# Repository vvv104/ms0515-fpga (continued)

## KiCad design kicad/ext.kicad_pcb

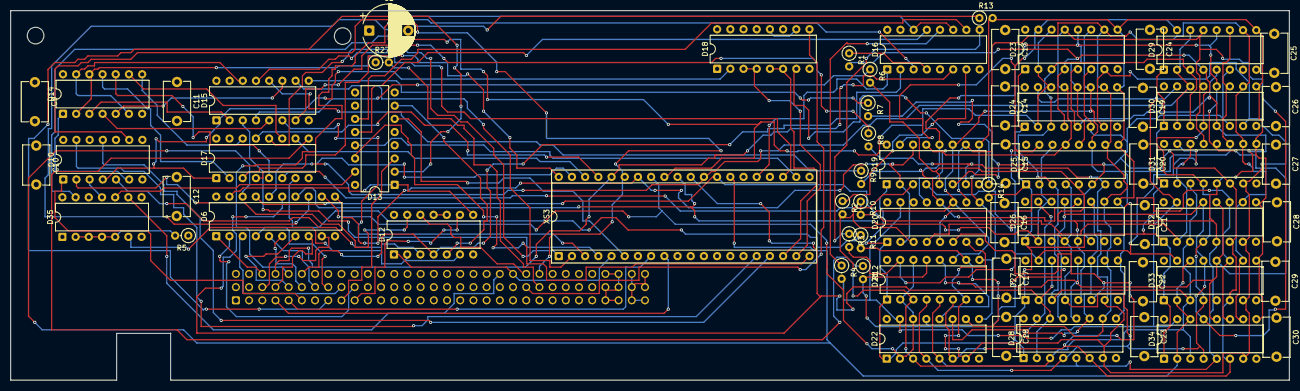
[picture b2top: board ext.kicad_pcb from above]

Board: 4 copper layers, 246.1 x 71.1 mm, 68 parts (1 on the bottom side), 102 nets.

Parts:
C1: 16В 33 мкФ ±20%; CP_Radial_D10.0mm_P7.50mm
C9, C10, C11, C12, C13, C14, C15, C16, C17, C18, C19, C20, C21, C22, C23, C24, C25, C26, C27, C28, C29, C30: 0,1 мкФ; C_Disc_D7.5mm_W5.0mm_P7.50mm
D6: К555АП6; DIP-20_W7.62mm
D10: К555ЛН1; DIP-14_W7.62mm
D12: К555ЛЛ1; DIP-14_W7.62mm
D13: КР531ИД14; DIP-16_W7.62mm
D14: К555ИЕ19; DIP-14_W7.62mm
D15, D16, D17: К555КП11; DIP-16_W7.62mm
D18: К555КП2; DIP-16_W7.62mm
D19, D20, D21, D22, D23, D24, D25, D26, D27, D28, D29, D30, D31, D32, D33, D34: КР565РУ7Г; DIP-16_W7.62mm
D35: К555ИР16; DIP-14_W7.62mm
H1, H2: Hole_3.2mm_NPTH
R1, R2, R3, R4, R6, R7, R8, R9, R10, R11, R12, R13, R14: 33 Ом; R_Axial_DIN0207_L6.3mm_D2.5mm_P2.54mm_Vertical
R5, R27: 4,7 кОм; R_Axial_DIN0207_L6.3mm_D2.5mm_P2.54mm_Vertical
XP1: plug, 96 (rows A, B, C of 32); DIN41612_C_3x32_Male_Horizontal_THT
XS3: DIP socket for D2; DIP-40_W15.24mm_Socket

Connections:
+5V: C1.1, C9.1, C10.1, C11.1, C12.1, C13.1, C14.1, C15.1, C16.1, C17.1, C18.1, C19.1, C20.1, C21.1, C22.1, C23.1, C24.1, C25.1, C26.1, C27.1, C28.1, C29.1, C30.1, D6.20, D10.14, D12.14, D13.16, D14.14, D15.16, D16.5, D16.16, D17.16, D18.16, D19.8, D20.8, D21.8, D22.8, D23.8, D24.8, D25.8, D26.8, D27.8, D28.8, D29.8, D30.8, D31.8, D32.8, D33.8, D34.8, D35.8, D35.14, R5.1, R27.1, XP1.a27, XP1.a28, XP1.b27, XP1.b28, XP1.c27, XP1.c28, XS3.26
+12V: XP1.a29, XP1.a30, XP1.b29, XP1.b30, XP1.c29, XP1.c30
-12V: XP1.a31, XP1.a32, XP1.b31, XP1.b32, XP1.c31, XP1.c32
CAS0: D19.15, D21.15, D23.15, D25.15, D27.15, D29.15, D31.15, D33.15, R3.2
CAS1: D20.15, D22.15, D24.15, D26.15, D28.15, D30.15, D32.15, D34.15, R4.2
CTS_B: D18.9, XP1.b23
DTR: D10.13, XS3.16
GND: C1.2, C9.2, C10.2, C11.2, C12.2, C13.2, C14.2, C15.2, C16.2, C17.2, C18.2, C19.2, C20.2, C21.2, C22.2, C23.2, C24.2, C25.2, C26.2, C27.2, C28.2, C29.2, C30.2, D6.10, D10.7, D12.7, D13.8, D14.7, D15.8, D15.15, D16.8, D16.15, D17.8, D17.15, D18.1, D18.8, D18.11, D18.13, D18.15, D19.16, D20.16, D21.16, D22.16, D23.16, D24.16, D25.16, D26.16, D27.16, D28.16, D29.16, D30.16, D31.16, D32.16, D33.16, D34.16, D35.1, D35.7, XP1.a1, XP1.a2, XP1.a19, XP1.a20, XP1.a25, XP1.a26, XP1.b1, XP1.b2, XP1.b19, XP1.b20, XP1.b25, XP1.b26, XP1.c1, XP1.c2, XP1.c15, XP1.c16, XP1.c25, XP1.c26, XS3.7
MA00: D14.3, D15.2
MA01: D14.4, D15.5
MA02: D14.5, D15.11
MA03: D14.6, D14.13, D15.14
MA04: D14.11, D17.2
MA05: D14.10, D17.5
MA06: D14.9, D17.11
MA07: D14.8, D17.14
MA08: D15.3, XS3.4
MA09: D15.6, XS3.3
MA10: D15.10, XS3.2
MA11: D15.13, XS3.1
MA12: D17.3, XS3.40
MA13: D17.6, XS3.39
MA14: D17.10, XS3.38
MA15: D17.13, XS3.37
MA16: D18.5, D18.6, XS3.18
MA17: D18.3, D18.4, XS3.19
RA0: D19.5, D20.5, D21.5, D22.5, D23.5, D24.5, D25.5, D26.5, D27.5, D28.5, D29.5, D30.5, D31.5, D32.5, D33.5, D34.5, R6.2
RA1: D19.7, D20.7, D21.7, D22.7, D23.7, D24.7, D25.7, D26.7, D27.7, D28.7, D29.7, D30.7, D31.7, D32.7, D33.7, D34.7, R8.2
RA2: D19.6, D20.6, D21.6, D22.6, D23.6, D24.6, D25.6, D26.6, D27.6, D28.6, D29.6, D30.6, D31.6, D32.6, D33.6, D34.6, R7.2
RA3: D19.12, D20.12, D21.12, D22.12, D23.12, D24.12, D25.12, D26.12, D27.12, D28.12, D29.12, D30.12, D31.12, D32.12, D33.12, D34.12, R9.2
RA4: D19.11, D20.11, D21.11, D22.11, D23.11, D24.11, D25.11, D26.11, D27.11, D28.11, D29.11, D30.11, D31.11, D32.11, D33.11, D34.11, R10.2
RA5: D19.10, D20.10, D21.10, D22.10, D23.10, D24.10, D25.10, D26.10, D27.10, D28.10, D29.10, D30.10, D31.10, D32.10, D33.10, D34.10, R11.2
RA6: D19.13, D20.13, D21.13, D22.13, D23.13, D24.13, D25.13, D26.13, D27.13, D28.13, D29.13, D30.13, D31.13, D32.13, D33.13, D34.13, R12.2
RA7: D19.9, D20.9, D21.9, D22.9, D23.9, D24.9, D25.9, D26.9, D27.9, D28.9, D29.9, D30.9, D31.9, D32.9, D33.9, D34.9, R13.2
RA8: D19.1, D20.1, D21.1, D22.1, D23.1, D24.1, D25.1, D26.1, D27.1, D28.1, D29.1, D30.1, D31.1, D32.1, D33.1, D34.1, R14.2
RAS: D19.4, D20.4, D21.4, D22.4, D23.4, D24.4, D25.4, D26.4, D27.4, D28.4, D29.4, D30.4, D31.4, D32.4, D33.4, D34.4, R1.2
RAS ОЗУ: D16.3, D35.13
RTS: D10.11, XS3.17
TC15: D35.9, XP1.c21
WE: D19.3, D20.3, D21.3, D22.3, D23.3, D24.3, D25.3, D26.3, D27.3, D28.3, D29.3, D30.3, D31.3, D32.3, D33.3, D34.3, R2.2
АД01: XP1.a4, XS3.9
АД02: XP1.a5, XS3.8
АД03: D10.1, XP1.a6
АД05: D13.2, XP1.a8
АД06: D13.3, XP1.a9
АД07: D12.9, XP1.a10
БАНК: D13.14, XS3.20
ВЫБОР ВВ55: D13.6, XS3.6
ВЫБОР ОЗУ: D12.5, D13.7
ГОТОВ В: D18.10, D18.12
ДЗП: D16.6, XP1.c4, XS3.36
ДК00: D6.11, D19.2, D19.14, D20.2, D20.14, XS3.34
ДК01: D6.12, D21.2, D21.14, D22.2, D22.14, XS3.33
ДК02: D6.13, D23.2, D23.14, D24.2, D24.14, XS3.32
ДК03: D6.14, D25.2, D25.14, D26.2, D26.14, XS3.31
ДК04: D6.15, D27.2, D27.14, D28.2, D28.14, XS3.30
ДК05: D6.16, D29.2, D29.14, D30.2, D30.14, XS3.29
ДК06: D6.17, D31.2, D31.14, D32.2, D32.14, XS3.28
ДК07: D6.18, D33.2, D33.14, D34.2, D34.14, XS3.27
ДЧТ: D6.1, XP1.c3
ДЧТ51: D12.1, XP1.c22, XS3.5
МК00: D6.9, XP1.b3
МК01: D6.8, XP1.b4
МК02: D6.7, XP1.b5
МК03: D6.6, XP1.b6
МК04: D6.5, XP1.b7
МК05: D6.4, XP1.b8
МК06: D6.3, XP1.b9
МК07: D6.2, XP1.b10
ОБМЕН: D6.19, D12.8, D13.1
ПВАК: D12.4, D16.2, XP1.c6
ПВАК0: D13.12, D16.13
ПВАК1: D13.11, D16.10
ПВАК ОЗУ: D13.15, D35.10
ПВАС: D16.11, D16.14, XP1.c5
ПЗУ: D13.13, XS3.22
РЕГЕНР: D16.1, XS3.25
СБРОС: D14.2, D14.12, XS3.23
СТАРТ: D10.9, XP1.c24, XS3.35
ТАКТ: D10.6, D14.1
выбор устр: D12.12, XP1.c23
запрос комм: R27.2, XP1.b24
соедн.01: D10.2, D12.13
соедн.02: D12.10, D12.11
соедн.03: D10.5, D12.3
соедн.04: D12.2, D12.6, D35.6
соедн.05: D16.4, R1.1
соедн.06: D16.7, R2.1
соедн.07: D16.9, R3.1
соедн.08: D16.12, R4.1
соедн.09: D35.2, D35.3, D35.4, D35.5, R5.2
соедн.10: D10.4, D15.1, D17.1, D18.2
соедн.11: D15.4, R6.1
соедн.12: D15.7, R8.1
соедн.13: D15.9, R7.1
соедн.14: D15.12, R9.1
соедн.15: D17.4, R10.1
соедн.16: D17.7, R11.1
соедн.17: D17.9, R12.1
соедн.18: D17.12, R13.1
соедн.19: D18.7, R14.1
соедн.37: D10.3, D35.11
